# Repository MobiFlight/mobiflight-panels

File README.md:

# Open Hardware Flight Simulator Panels

MobiFlight uses openly designed Arduino modules to connect buttons and switches and lights to most commonly used flight simulator software. These panels are openly licensed, meaning you can use, improve, share and build them, even for others if you have the skills and tools, but we kindly ask that you share your improvements back to others, if you choose to build upon them. This is a work in progress.

You can configure the panels using Mobiflight, without depending on closed and proprietary drivers and software that might or might not support the simulator software and simulated aircraft of your choice.

## Based on a template system

See the [Mobiflight Panel Template](https://github.com/Mobiflight/mobiflight-templates) for the SVG design asset
library that was used to create these.

These panels are intended for flight simulation, they utilize Arduino hardware, and generally will feature a circuit board
that is mounted behind the panel with 10mm nylon spacers. The finished panels can be connected to Microsoft Flight Simulator 
2020 (msfs2020) or other flight simulator software using Mobiflight open source software. See the 
[MobiFlight website](http://www.mobiflight.com) for more information, and join our Discord server at https://discord.gg/99vHbK7

These are work in progress, contributions are welcome via github pull requests, or if you want to coordinate or have questions, please file an issue.

The design philosophy is to replicate the functionality of real aircraft panels, with realistic looking elements and labeling, but not intending to be a 1:1 accurate replica to the millimeter dimensions. The result look convincing and have the feel of a real airplane cockpits, while enabling you to do 
layouts quickly, and using commonly available hardware as much as possible. 

The panel sizes use the "dzus" mounting standard used in many airplane cockpits, so that different panels can be stacked together and share the same width as much as possible. Some panels naturally might be different like certain panels on A320 center pedestal and overhead panels, but the intention is to adapt the standard as much as practically possible.

## How to edit / view the files

The panel design is a SVG file intended to be used with [Inkscape](http://www.inkscape.org),
and it is laid out with red and black so that it is compatible with a workflow using
[K40 Whisperer](https://www.scorchworks.com/K40whisperer/k40whisperer.html) and a CO2 
laser cutter, to cut and engrave the panels out of acrylic plastic sheet.

The PCB design JSON files can be opened with EasyEDA PCB design suite, accessible at www.easyeda.com. 
On the EasyEDA editor, select "Document" > "Open" > "EasyEDA Source" to import both JSON files into the editor.
One of them is the wiring schema, and the other one is the pcboard itself.

## Mind the gap!

Note, that as this is a pretty monumental work in progress, and the idea is to do this together as a community, we try to share designs earlier rather than later. For this reason, designs might not be final, complete or even fully functional, although we try to have functional stuff in the repository. When some
designs depend on certain 3D-printed button gaps or other hardware, that should be ideally noted in the README file.

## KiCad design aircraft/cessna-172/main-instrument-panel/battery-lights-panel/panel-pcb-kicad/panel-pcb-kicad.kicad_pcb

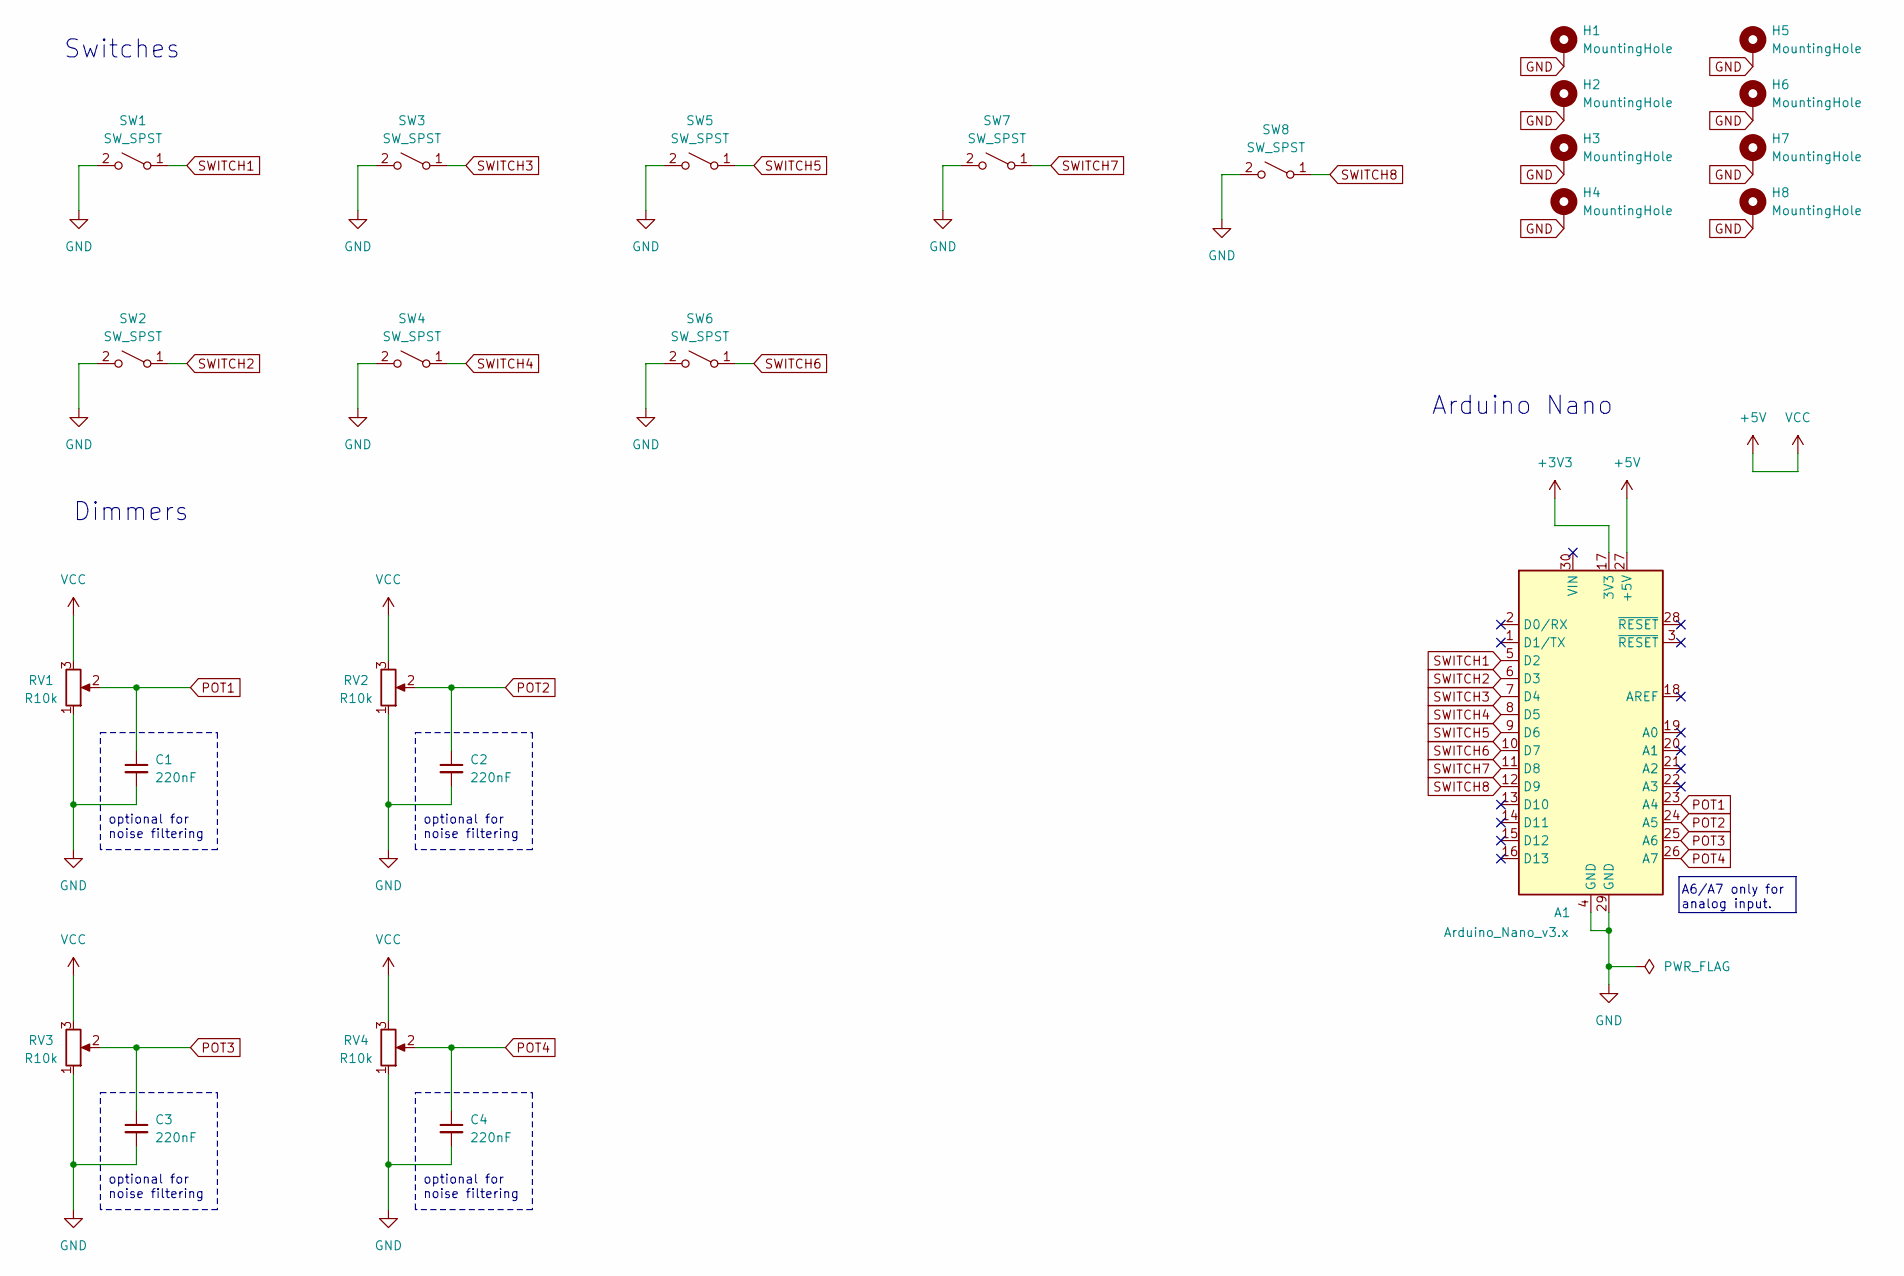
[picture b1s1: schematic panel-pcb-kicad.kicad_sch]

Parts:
A1: Arduino_Nano_v3.x; Arduino_Nano_WithMountingHoles
C1, C2, C3, C4: 220nF; C_Disc_D7.0mm_W2.5mm_P5.00mm
H1, H2, H3, H4, H5, H6, H7, H8: MountingHole; MountingHole_3.2mm_M3_ISO14580_Pad_TopBottom
RV1, RV2, RV3, RV4: R10k; Potentiometer_Alps_RK09K_Single_Vertical
SW1, SW2, SW3, SW4, SW5, SW6, SW7, SW8: SW_SPST; T8013

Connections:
+3V3: A1.17 (3V3)
GND: A1.4 (GND), A1.29 (GND), C1.2, C2.2, C3.2, C4.2, H1.1 (1_1), H2.1 (1_1), H3.1 (1_1), H4.1 (1_1), H5.1 (1_1), H6.1 (1_1), H7.1 (1_1), H8.1 (1_1), RV1.1, RV2.1, RV3.1, RV4.1, SW1.2 (B), SW2.2 (B), SW3.2 (B), SW4.2 (B), SW5.2 (B), SW6.2 (B), SW7.2 (B), SW8.2 (B)
POT1: A1.23 (A4), C1.1, RV1.2
POT2: A1.24 (A5), C2.1, RV2.2
POT3: A1.25 (A6), C3.1, RV3.2
POT4: A1.26 (A7), C4.1, RV4.2
SWITCH1: A1.5 (D2), SW1.1 (A)
SWITCH2: A1.6 (D3), SW2.1 (A)
SWITCH3: A1.7 (D4), SW3.1 (A)
SWITCH4: A1.8 (D5), SW4.1 (A)
SWITCH5: A1.9 (D6), SW5.1 (A)
SWITCH6: A1.10 (D7), SW6.1 (A)
SWITCH7: A1.11 (D8), SW7.1 (A)
SWITCH8: A1.12 (D9), SW8.1 (A)
VBUS: A1.27 (+5V), RV1.3, RV2.3, RV3.3, RV4.3

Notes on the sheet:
A6/A7 only for analog input.
optional for noise filtering
Arduino Nano
Dimmers
Switches

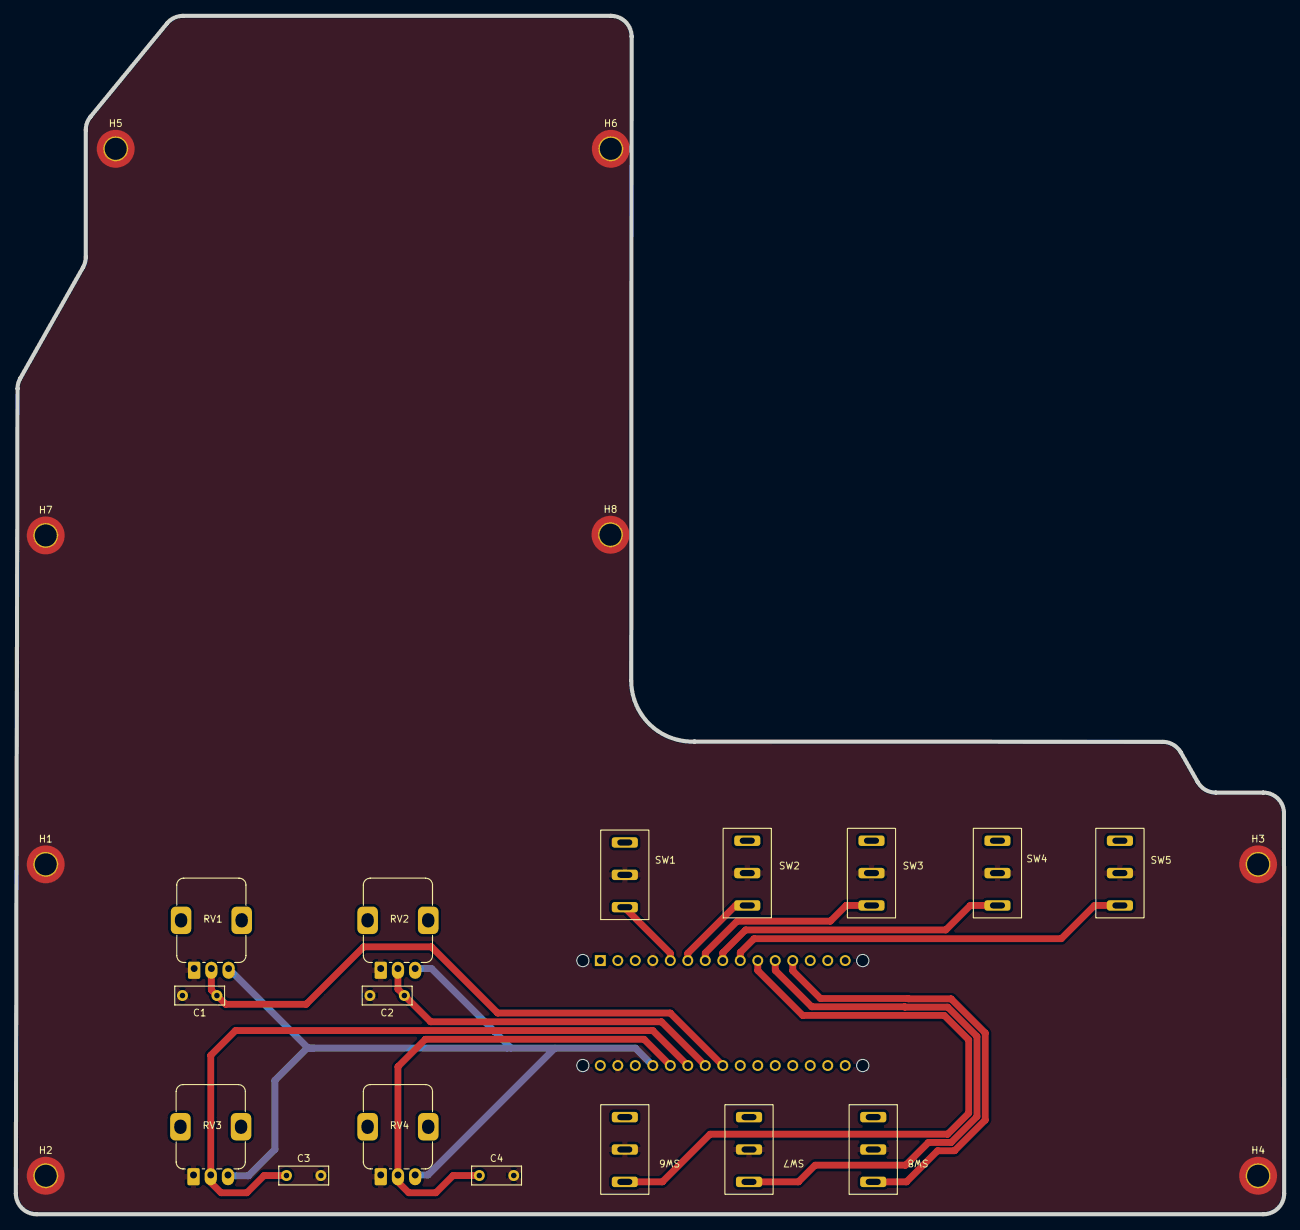
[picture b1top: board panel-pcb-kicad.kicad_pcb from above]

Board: 2 copper layers, 184.1 x 174.0 mm, 25 parts (1 on the bottom side), 14 nets.

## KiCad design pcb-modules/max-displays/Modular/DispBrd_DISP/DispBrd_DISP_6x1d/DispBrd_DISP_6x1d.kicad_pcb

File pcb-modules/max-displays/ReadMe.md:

## General description
This repository contains the [KiCad](https://www.kicad.org/) projects (Schematics, PCBs, Gerber files) for a variety of generic 3- to 6-digit display panels.

There are two types of designs: _One-piece_ and _Modular_. The former is a complete panel, the latter has a 
separate driver board that fits any of the different display carrier boards.

## Common features
 * MAX7219 drivers _(DIP for one-piece, DIP or SMD variants for modular)_
 * 0.36" LED displays
 * Several combinations of display components for a given number of digits _(see list below)_
 
## Display Variants
The LED display types to be mounted are listed below for each variant.

#### One-piece design:
 * 1x 4-digit
 * 1x 5-digit
 * 1x 6-digit

#### Modular design:
 * 1x 3-digit
 * 1x 4-digit
 * 1x 5-digit
 * 1x 6-digit
 * 1x 5-digit, side mounting holes
 * 1x 6-digit, side mounting holes
 * 1x 3-digit + 1x 2-digit
 * 2x 3-digit
 * 6x 1-digit

#### Notes:
 * **_Displays must be common CATHODE._**
 * some LED display sizes have compatible pinout, in particular:
    * A 3-digit display can be mounted in place of a 4- or 5-digit display, but the rightmost digit will then  correspond to digit #2 or #3 (i.e. 1 or 2 rightmost digits are lost)
    * A 4-digit display can be mounted in place of a 5-digit display, same caveats as above.
 
## Components
Beside the MAX7219 ICs and the LED displays of the chosen types, other components required are:

|Qty |Value |Desc |
|-----|-------|------|
| 1x |10uF/16V THD |Electrolytic capacitor|
| 1x |100nF 1206 SMD |Ceramic capacitor (MLCC)|
| 1x |10k 0.25W THD|Resistor(*)|
|    |0.1" |F header strips, tulip type (for display sockets)|
|    |0.1" |M/F (as required) connectors or header strips for board-to-board and external connections|

(*) The resistor value might have to be adjusted according to the displays used in order to obtain the desired brightness; please refer to the MAX7219 datasheet for further details.

### Notes
The designs can be opened and modified with [__KiCad version 5.99__ nightly build](https://kicad-downloads.s3.cern.ch/index.html?prefix=windows/nightly/) (soon to become 6.0 official);
make sure that you use a build that is more recent than Nov 1st 2021.
KiCad is not required if you are just interested in having the PCBs manufactured; a .zip with set of ready Gerber files is provided (compliant with the requirements of the JLCPCB online ordering service, but also of other online services). However, having KiCad installed allows you to modify the design, reissue the Gerber files and check them with the integrated Gerber viewer.

### License

This work is licensed under a [Creative Commons Attribution-ShareAlike 4.0 International License](http://creativecommons.org/licenses/by-sa/4.0/).

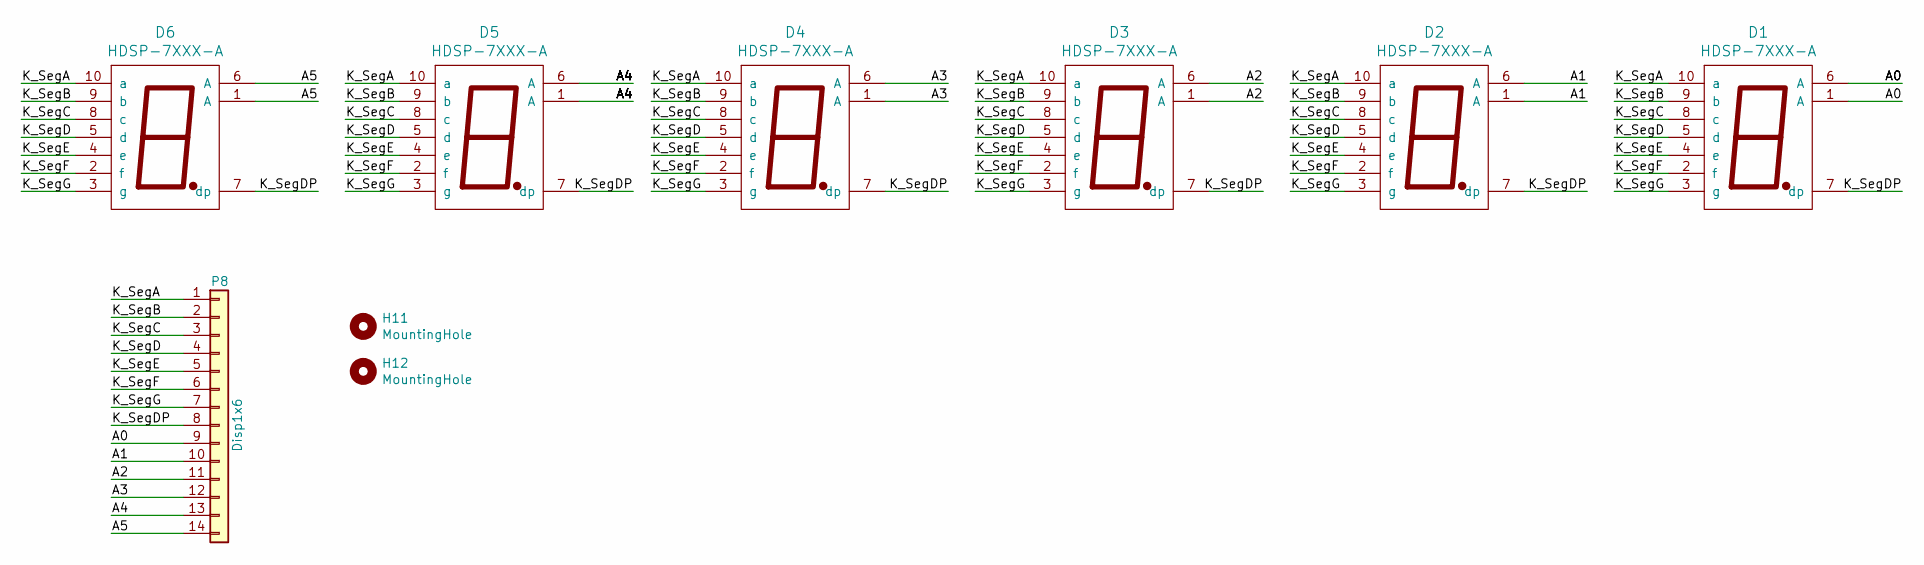
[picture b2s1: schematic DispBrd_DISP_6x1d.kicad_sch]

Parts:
D1, D2, D3, D4, D5, D6: HDSP-7XXX-A; Disp7_036
H11, H12: MountingHole; Hole3mm
P8: Disp1x6; IDC-Header_2x07_P2.54mm_Vertical

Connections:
/A0: D1.1 (A), D1.6 (A), P8.9
/A1: D2.1 (A), D2.6 (A), P8.10
/A2: D3.1 (A), D3.6 (A), P8.11
/A3: D4.1 (A), D4.6 (A), P8.12
/A4: D5.1 (A), D5.6 (A), P8.13
/A5: D6.1 (A), D6.6 (A), P8.14
/K_SegA: D1.10 (a), D2.10 (a), D3.10 (a), D4.10 (a), D5.10 (a), D6.10 (a), P8.1
/K_SegB: D1.9 (b), D2.9 (b), D3.9 (b), D4.9 (b), D5.9 (b), D6.9 (b), P8.2
/K_SegC: D1.8 (c), D2.8 (c), D3.8 (c), D4.8 (c), D5.8 (c), D6.8 (c), P8.3
/K_SegD: D1.5 (d), D2.5 (d), D3.5 (d), D4.5 (d), D5.5 (d), D6.5 (d), P8.4
/K_SegDP: D1.7 (dp), D2.7 (dp), D3.7 (dp), D4.7 (dp), D5.7 (dp), D6.7 (dp), P8.8
/K_SegE: D1.4 (e), D2.4 (e), D3.4 (e), D4.4 (e), D5.4 (e), D6.4 (e), P8.5
/K_SegF: D1.2 (f), D2.2 (f), D3.2 (f), D4.2 (f), D5.2 (f), D6.2 (f), P8.6
/K_SegG: D1.3 (g), D2.3 (g), D3.3 (g), D4.3 (g), D5.3 (g), D6.3 (g), P8.7

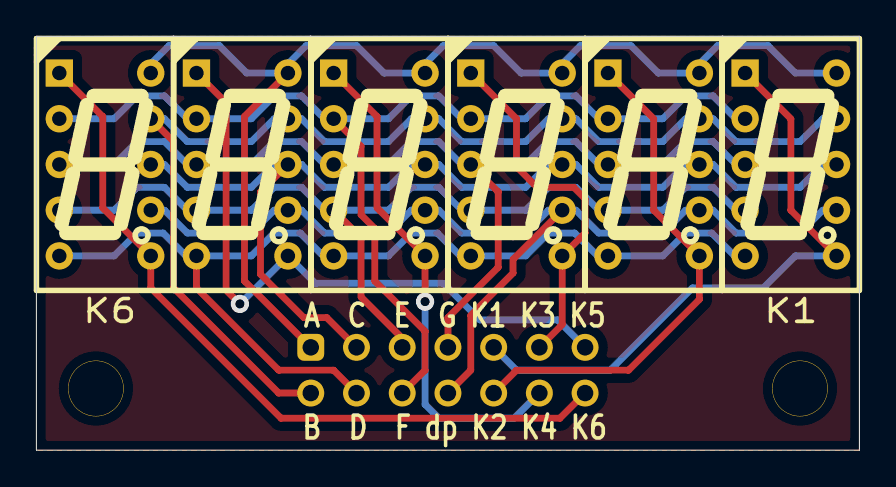
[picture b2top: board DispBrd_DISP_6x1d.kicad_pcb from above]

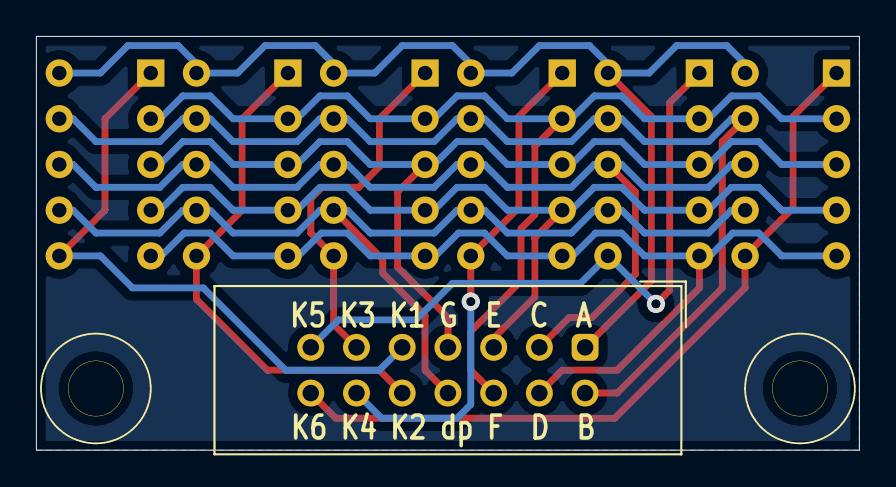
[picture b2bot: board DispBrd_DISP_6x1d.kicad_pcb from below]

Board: 2 copper layers, 45.7 x 23.0 mm, 9 parts (3 on the bottom side), 14 nets.

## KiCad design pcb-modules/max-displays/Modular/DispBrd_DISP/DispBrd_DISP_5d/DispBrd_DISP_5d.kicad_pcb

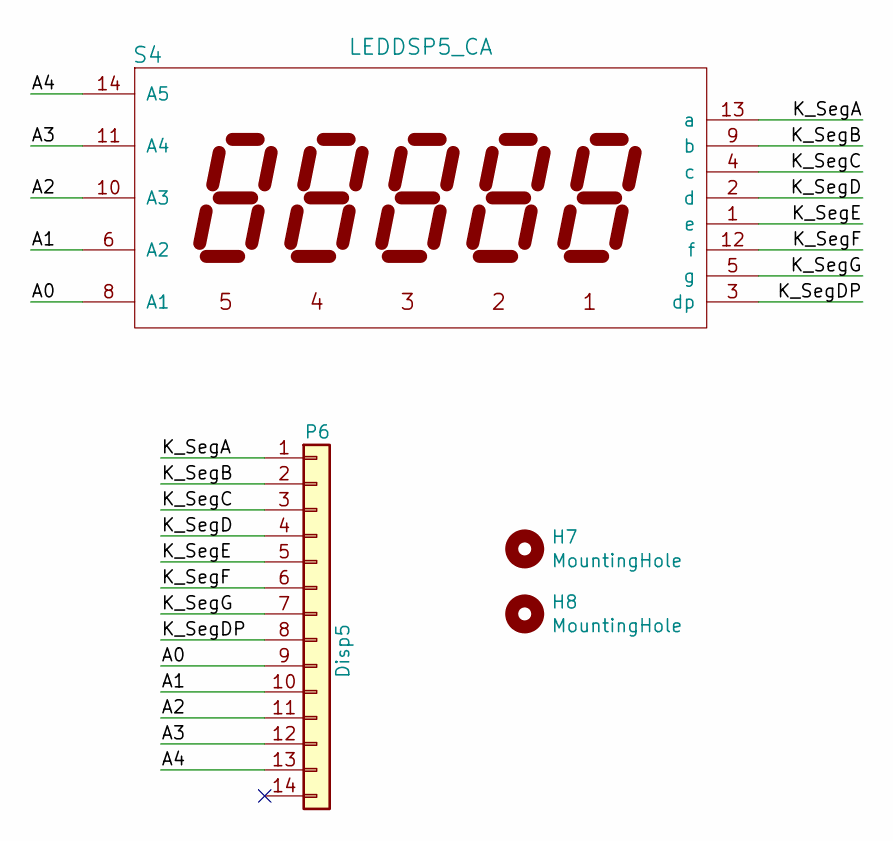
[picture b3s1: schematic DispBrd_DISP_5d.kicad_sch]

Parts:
H7, H8: MountingHole; Hole3mm
P6: Disp5; IDC-Header_2x07_P2.54mm_Vertical
S4: LEDDSP5_CA; Disp7s5x_036

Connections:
/A0: P6.9, S4.8 (A1)
/A1: P6.10, S4.6 (A2)
/A2: P6.11, S4.10 (A3)
/A3: P6.12, S4.11 (A4)
/A4: P6.13, S4.14 (A5)
/K_SegA: P6.1, S4.13 (a)
/K_SegB: P6.2, S4.9 (b)
/K_SegC: P6.3, S4.4 (c)
/K_SegD: P6.4, S4.2 (d)
/K_SegDP: P6.8, S4.3 (dp)
/K_SegE: P6.5, S4.1 (e)
/K_SegF: P6.6, S4.12 (f)
/K_SegG: P6.7, S4.5 (g)

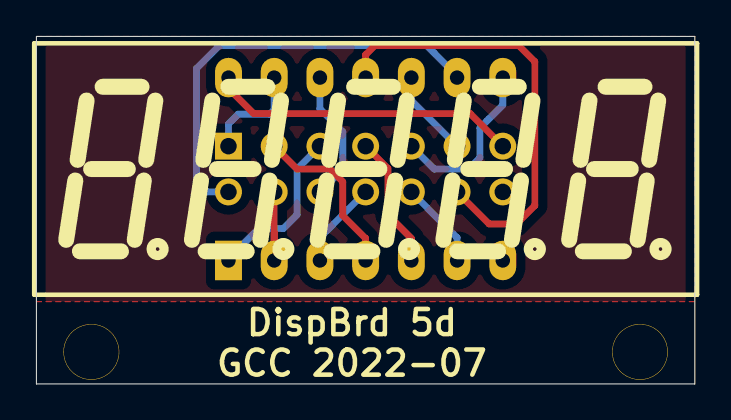
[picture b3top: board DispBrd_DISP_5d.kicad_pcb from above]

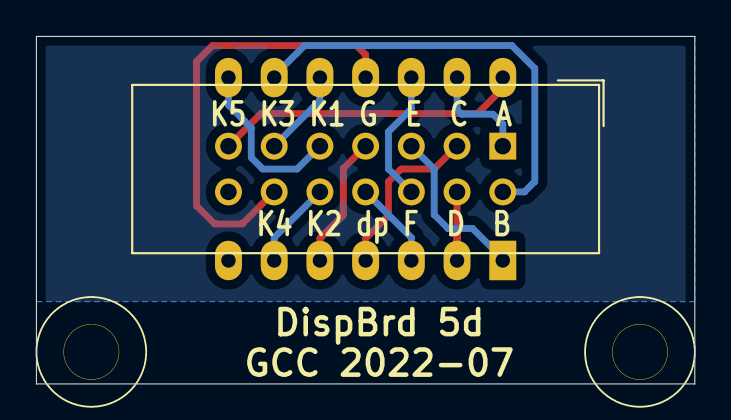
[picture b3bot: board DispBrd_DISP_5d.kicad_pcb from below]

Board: 2 copper layers, 36.6 x 19.3 mm, 4 parts (3 on the bottom side), 13 nets.

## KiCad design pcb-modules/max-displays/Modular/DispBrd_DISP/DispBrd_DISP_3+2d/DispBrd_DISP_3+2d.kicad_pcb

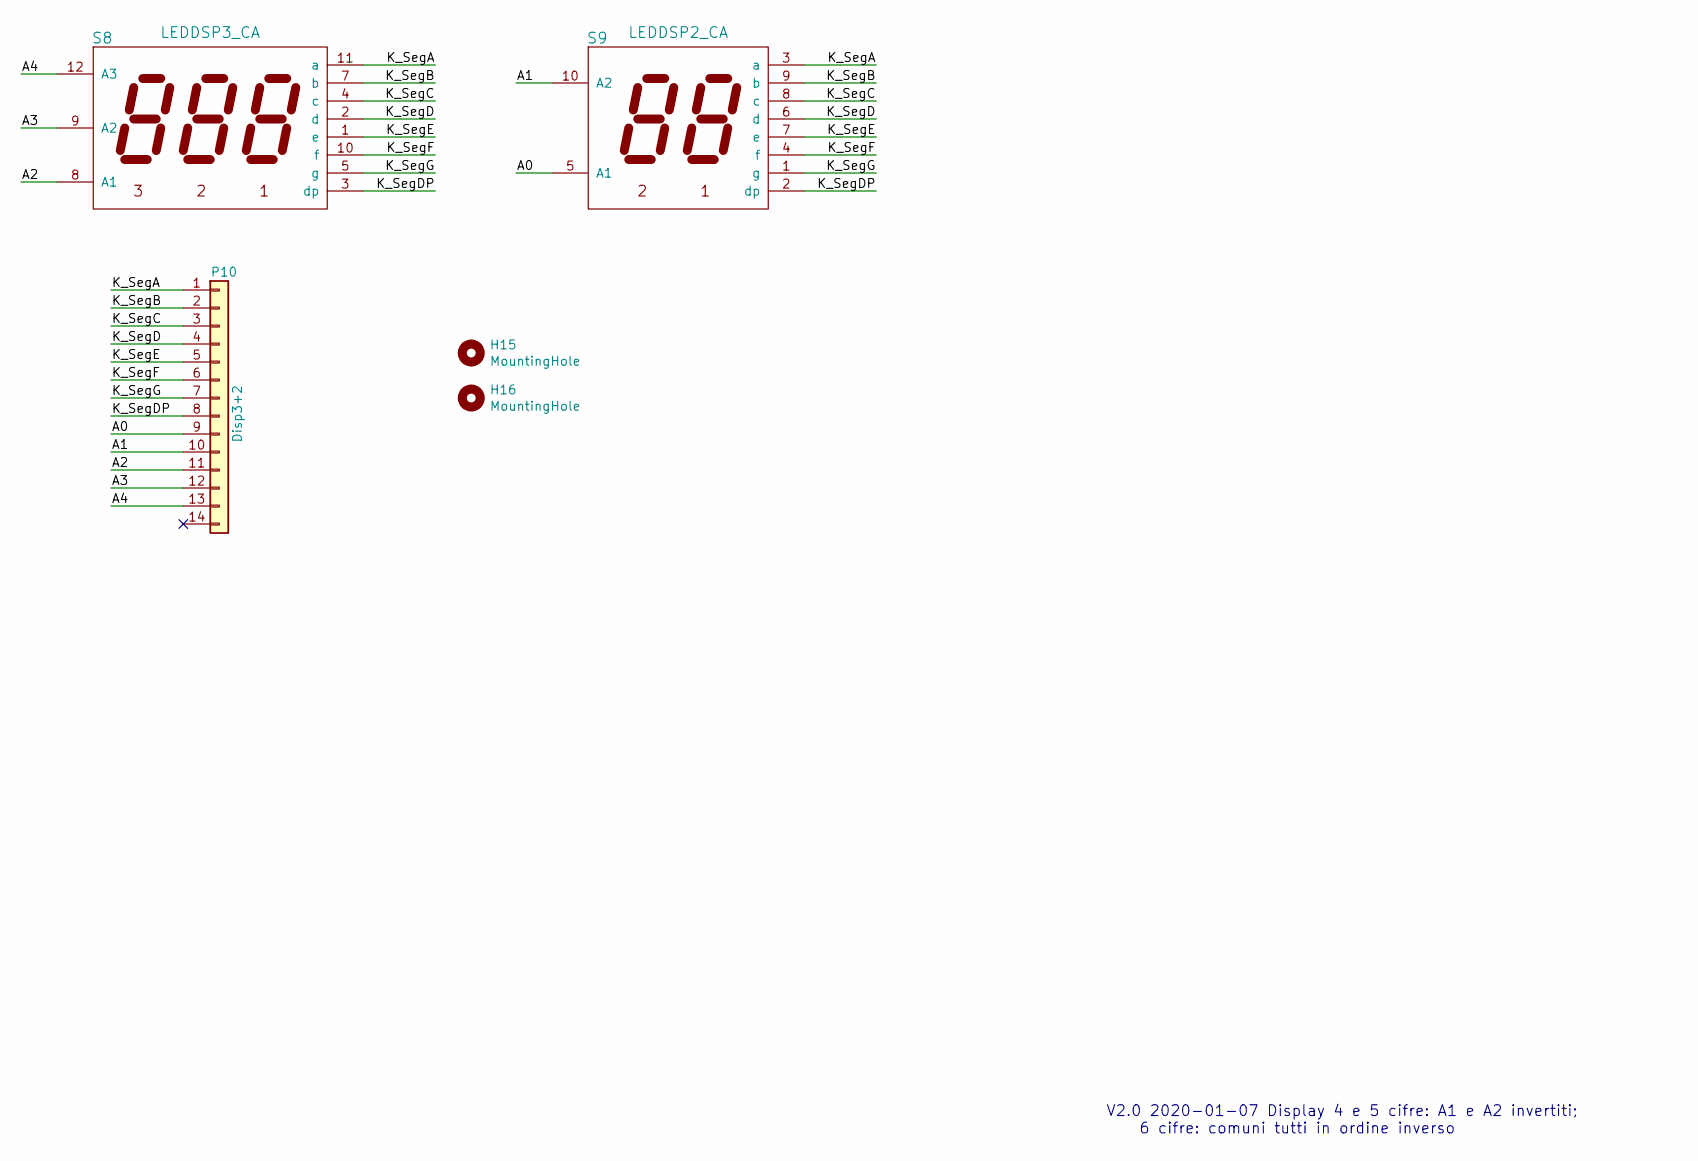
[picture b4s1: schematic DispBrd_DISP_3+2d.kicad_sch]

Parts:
H15, H16: MountingHole; Hole3mm
P10: Disp3+2; IDC-Header_2x07_P2.54mm_Vertical
S8: LEDDSP3_CA; Disp7s3x_036
S9: LEDDSP2_CA; Disp7s2x_036

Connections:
/A0: P10.9, S9.5 (A1)
/A1: P10.10, S9.10 (A2)
/A2: P10.11, S8.8 (A1)
/A3: P10.12, S8.9 (A2)
/A4: P10.13, S8.12 (A3)
/K_SegA: P10.1, S8.11 (a), S9.3 (a)
/K_SegB: P10.2, S8.7 (b), S9.9 (b)
/K_SegC: P10.3, S8.4 (c), S9.8 (c)
/K_SegD: P10.4, S8.2 (d), S9.6 (d)
/K_SegDP: P10.8, S8.3 (dp), S9.2 (dp)
/K_SegE: P10.5, S8.1 (e), S9.7 (e)
/K_SegF: P10.6, S8.10 (f), S9.4 (f)
/K_SegG: P10.7, S8.5 (g), S9.1 (g)

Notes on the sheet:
V2.0 2020-01-07 Display 4 e 5 cifre: A1 e A2 invertiti; 6 cifre: comuni tutti in ordine inverso

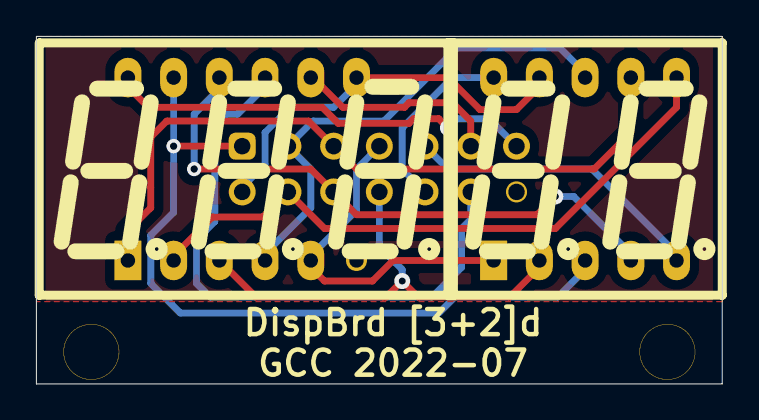
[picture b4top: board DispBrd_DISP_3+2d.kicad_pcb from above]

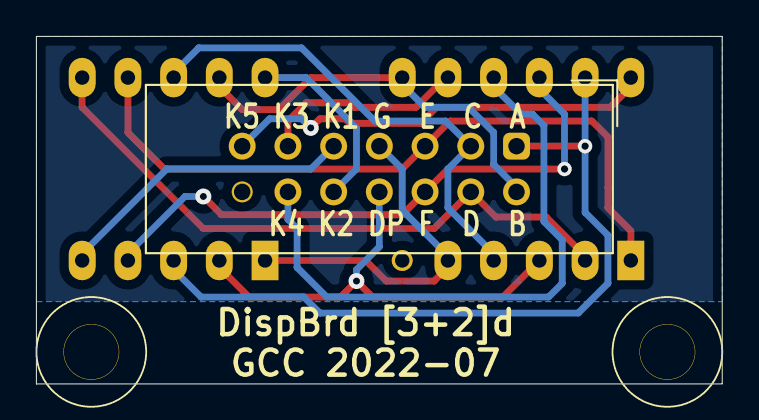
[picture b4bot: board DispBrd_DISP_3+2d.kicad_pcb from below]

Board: 2 copper layers, 38.1 x 19.3 mm, 5 parts (3 on the bottom side), 13 nets.

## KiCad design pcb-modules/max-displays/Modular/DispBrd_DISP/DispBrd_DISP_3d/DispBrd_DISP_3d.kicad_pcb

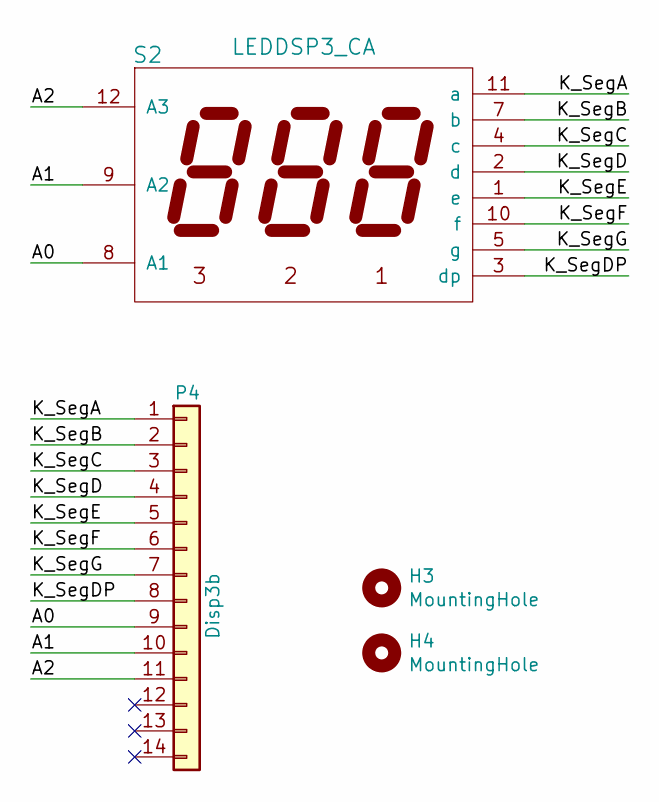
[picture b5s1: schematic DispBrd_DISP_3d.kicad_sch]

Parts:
H3, H4: MountingHole; Hole3mm
P4: Disp3b; IDC-Header_2x07_P2.54mm_Vertical
S2: LEDDSP3_CA; Disp7s3x_036

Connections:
/A0: P4.9, S2.8 (A1)
/A1: P4.10, S2.9 (A2)
/A2: P4.11, S2.12 (A3)
/K_SegA: P4.1, S2.11 (a)
/K_SegB: P4.2, S2.7 (b)
/K_SegC: P4.3, S2.4 (c)
/K_SegD: P4.4, S2.2 (d)
/K_SegDP: P4.8, S2.3 (dp)
/K_SegE: P4.5, S2.1 (e)
/K_SegF: P4.6, S2.10 (f)
/K_SegG: P4.7, S2.5 (g)

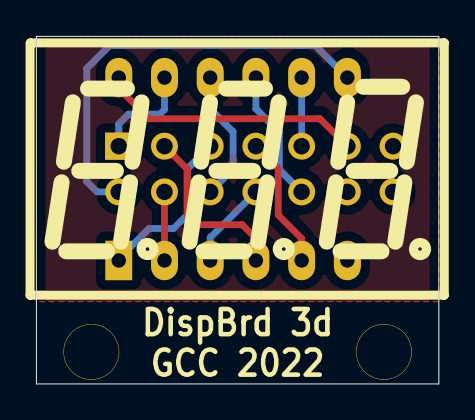
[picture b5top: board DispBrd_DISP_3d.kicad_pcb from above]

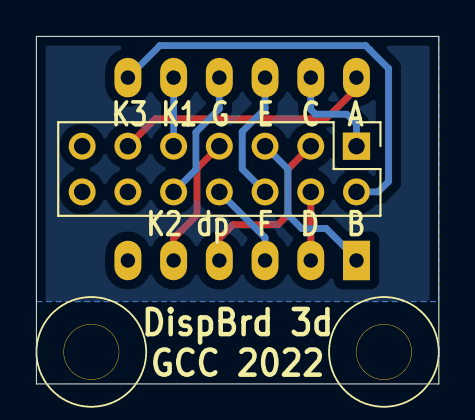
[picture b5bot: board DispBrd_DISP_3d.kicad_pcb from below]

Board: 2 copper layers, 22.4 x 19.3 mm, 4 parts (3 on the bottom side), 11 nets.

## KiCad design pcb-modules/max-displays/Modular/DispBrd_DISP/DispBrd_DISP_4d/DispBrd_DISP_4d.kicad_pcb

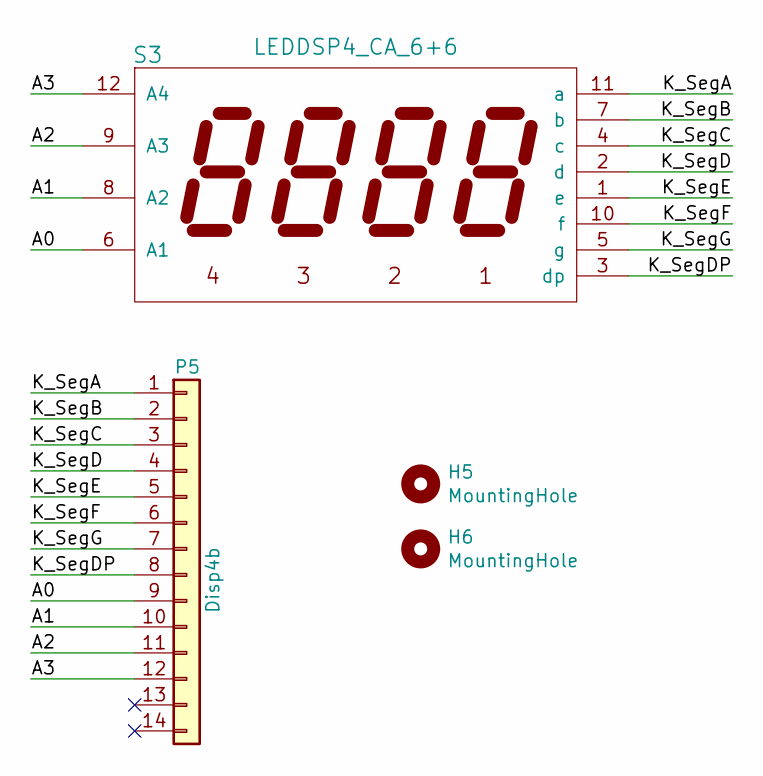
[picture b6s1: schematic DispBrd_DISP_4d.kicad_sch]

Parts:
H5, H6: MountingHole; Hole3mm
P5: Disp4b; IDC-Header_2x07_P2.54mm_Vertical
S3: LEDDSP4_CA_6+6; Disp7s4x_036_6+6

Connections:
/A0: P5.9, S3.6 (A1)
/A1: P5.10, S3.8 (A2)
/A2: P5.11, S3.9 (A3)
/A3: P5.12, S3.12 (A4)
/K_SegA: P5.1, S3.11 (a)
/K_SegB: P5.2, S3.7 (b)
/K_SegC: P5.3, S3.4 (c)
/K_SegD: P5.4, S3.2 (d)
/K_SegDP: P5.8, S3.3 (dp)
/K_SegE: P5.5, S3.1 (e)
/K_SegF: P5.6, S3.10 (f)
/K_SegG: P5.7, S3.5 (g)

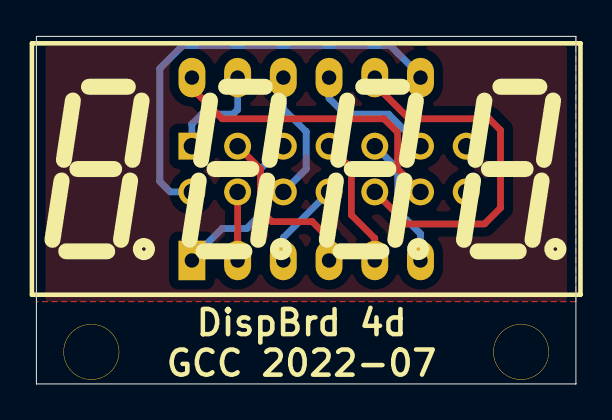
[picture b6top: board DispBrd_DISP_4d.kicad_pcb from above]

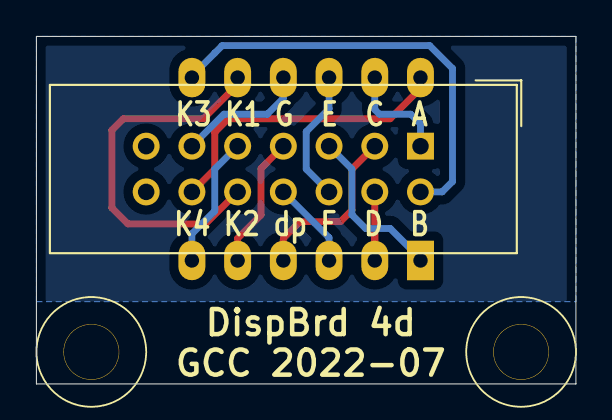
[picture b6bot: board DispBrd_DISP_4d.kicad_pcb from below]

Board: 2 copper layers, 30.0 x 19.3 mm, 4 parts (3 on the bottom side), 12 nets.

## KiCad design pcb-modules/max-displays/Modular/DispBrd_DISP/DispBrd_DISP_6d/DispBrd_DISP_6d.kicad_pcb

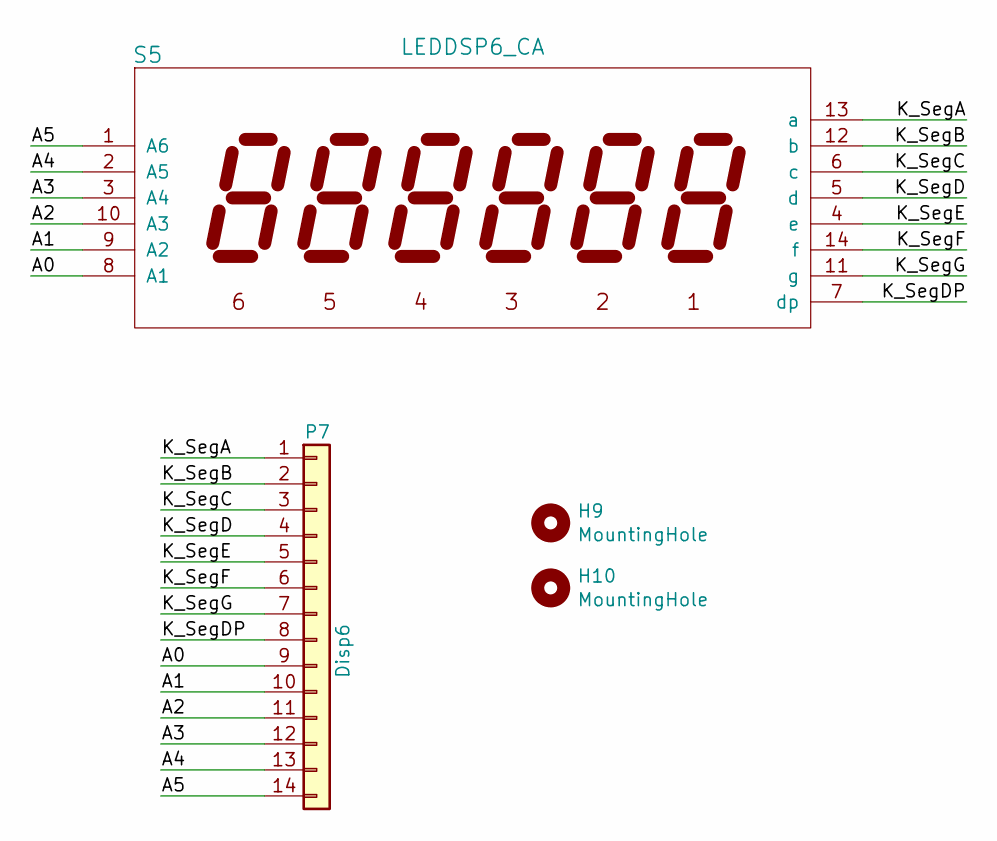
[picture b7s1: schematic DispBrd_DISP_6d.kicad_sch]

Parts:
H9, H10: MountingHole; Hole3mm
P7: Disp6; IDC-Header_2x07_P2.54mm_Vertical
S5: LEDDSP6_CA; Disp7s6x_036

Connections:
/A0: P7.9, S5.8 (A1)
/A1: P7.10, S5.9 (A2)
/A2: P7.11, S5.10 (A3)
/A3: P7.12, S5.3 (A4)
/A4: P7.13, S5.2 (A5)
/A5: P7.14, S5.1 (A6)
/K_SegA: P7.1, S5.13 (a)
/K_SegB: P7.2, S5.12 (b)
/K_SegC: P7.3, S5.6 (c)
/K_SegD: P7.4, S5.5 (d)
/K_SegDP: P7.8, S5.7 (dp)
/K_SegE: P7.5, S5.4 (e)
/K_SegF: P7.6, S5.14 (f)
/K_SegG: P7.7, S5.11 (g)

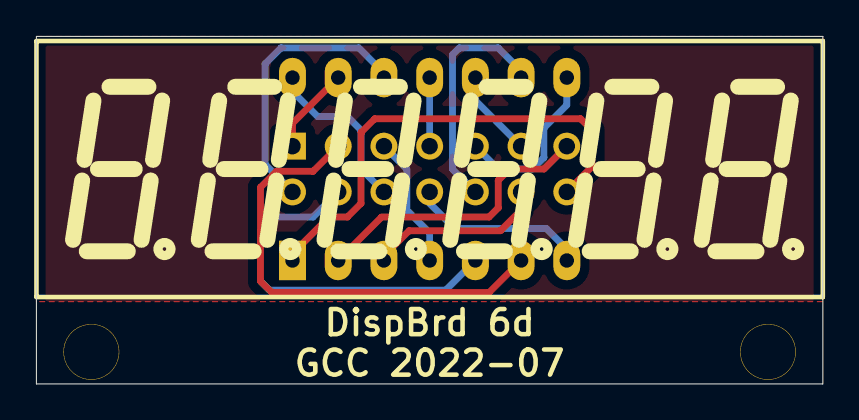
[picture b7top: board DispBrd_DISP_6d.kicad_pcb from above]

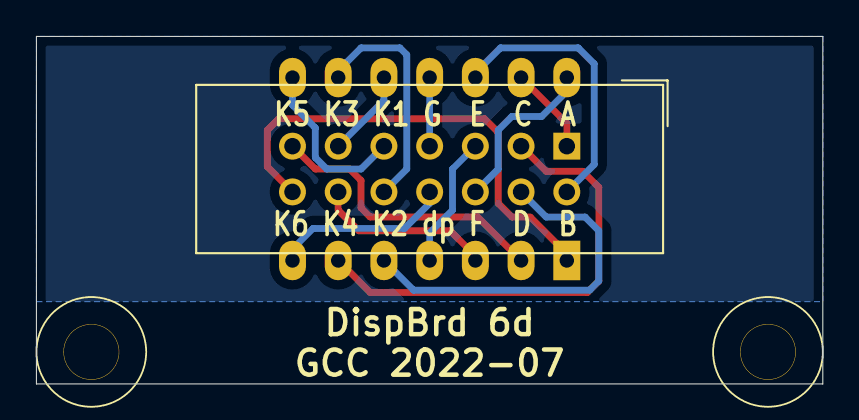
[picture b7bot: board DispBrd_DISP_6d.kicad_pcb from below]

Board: 2 copper layers, 43.7 x 19.3 mm, 4 parts (3 on the bottom side), 14 nets.
